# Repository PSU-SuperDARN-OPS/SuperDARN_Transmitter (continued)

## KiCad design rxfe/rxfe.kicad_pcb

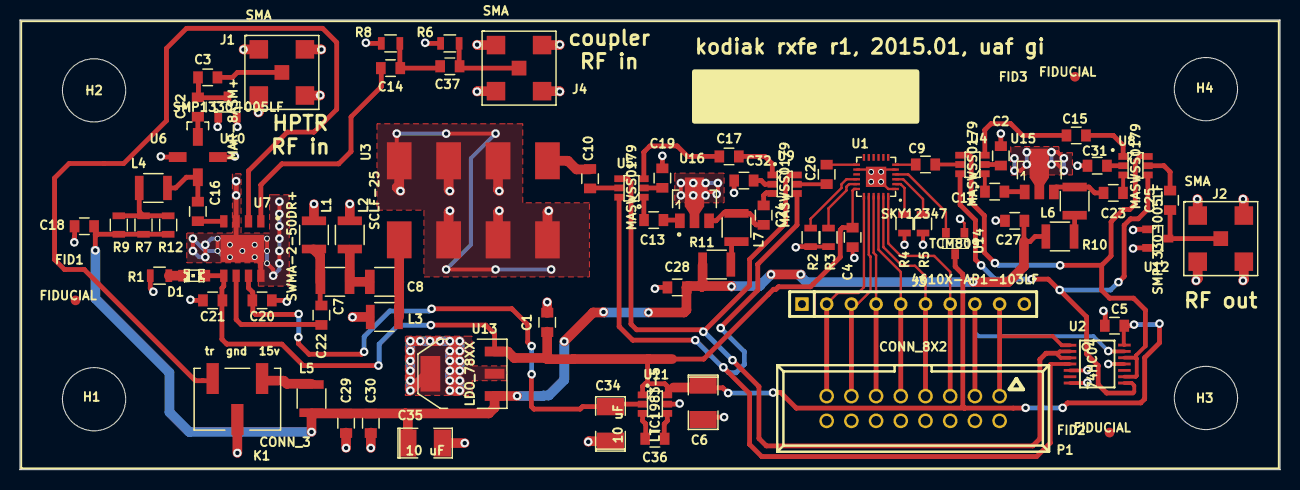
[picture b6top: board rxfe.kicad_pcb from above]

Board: 2 copper layers, 129.5 x 46.2 mm, 85 parts (0 on the bottom side), 65 nets.

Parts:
C1, C4, C5, C18, C20, C21, C27, C28, C29: 100 nF; C_0805
C2, C3, C9, C10, C11, C12, C13, C14, C15, C16, C17, C19, C22, C23, C24, C25, C26, C31, C32, C37: 22 nF; C_0805
C6, C34, C35: 10 uF; SMD-1210_Pol
C7, C8: 680pF; C_1210
C30, C36: 1 uF; C_0805
D1: LED; LED-0805
FID1, FID2, FID3: FIDUCIAL; FID_1MM
H1, H2, H3, H4: MOUNTING_HOLE; MountingHole_6-5mm
J1, J2, J4: SMA; SMA_0732511350
J3: 4610X-AP1-103LF; SIL-10
K1: CONN_3; 0740991003
L1, L3, L4, L5, L6, L7: 3.9uH; R_1210
L2: 1.2uH; R_1210
P1: CONN_8X2; VASCH8x2
R1, R2, R3, R4, R5, R7, R9, R12: 1k; R_0805
R6, R8: DNP; R_0805
R10, R11: 93.1; R_1210
U1: SKY12347; qfn24
U2: 74HC04; TSSOP14
U3: SCLF-25; YY161
U4, U5, U8, U9: MASWSS0179; SOT-23-6
U6: MAR-8ASM+; WW107
U7: SWMA-2-50DR+; DL1020
U10, U12: SMP1330-005LF; SOT-23
U11: LTC1983-5; SOT-23-6
U13: LDO_78XX; SOT-223
U14: TCM809; SOT-23
U15, U16: GALI-84+; SOT89-3_Housing

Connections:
-5V: C20.1, C34.2, U7.7, U11.2
/AMP1: U2.4, U5.6, U9.4
/AMP1CTL: J3.9, P1.1, U2.1
/AMP2: U2.8, U4.6, U8.4
/AMP2CTL: J3.8, P1.3, U2.13
/T/R: K1.3, U7.2
/~AMP1: U2.2, U2.3, U5.4, U9.6
/~AMP2: U2.9, U2.12, U4.4, U8.6
GND: C1.2, C2.1, C4.2, C5.2, C6.2, C18.1, C19.1, C20.2, C21.1, C27.1, C28.1, C29.2, C30.2, C31.2, C32.2, C34.1, C35.2, J1.2, J1.3, J1.4, J1.5, J2.2, J2.3, J2.4, J2.5, J3.1, J3.10, J4.2, J4.3, J4.4, J4.5, K1.2, L1.2, L2.2, L3.2, P1.2, P1.4, P1.6, P1.8, P1.10, P1.12, P1.14, P1.16, R1.2, R2.2, R3.2, R4.2, R5.2, R6.1, R8.1, U1.1, U1.5, U1.14, U1.25, U2.5, U2.7, U2.11, U3.2, U3.3, U3.4, U3.5, U3.6, U3.7, U6.2, U6.4, U7.3, U7.8, U7.EP, U10.1, U10.2, U11.5, U12.1, U12.2, U13.2, U13.4, U14.1, U15.2, U16.2
unnamed: C2.2, U4.2
unnamed: C3.2, J1.1
unnamed: C7.1, C8.2, L2.1
unnamed: C8.1, L3.1, U3.1
unnamed: C9.1, U4.5
unnamed: C9.2, U1.6
unnamed: C10.1, U5.5
unnamed: C10.2, U3.8
unnamed: C11.1, U15.1
unnamed: C11.2, U4.1
unnamed: C12.1, U6.1
unnamed: C3.1, C12.2, U10.3
unnamed: C13.1, U16.1
unnamed: C13.2, U5.1
unnamed: C14.1, U7.1
unnamed: C14.2, C37.1, R8.2
unnamed: C15.1, U8.1
unnamed: C15.2, U4.3
unnamed: C16.1, U7.4
unnamed: C16.2, L4.1, U6.3
unnamed: C17.1, U9.1
unnamed: C17.2, U5.3
unnamed: C19.2, U5.2
unnamed: C22.1, U7.6
unnamed: C7.2, C22.2, L1.1
unnamed: C23.1, U8.3
unnamed: C23.2, L6.1, U15.3
unnamed: C24.1, U9.3
unnamed: C24.2, L7.1, U16.3
unnamed: C25.1, J2.1, U12.3
unnamed: C25.2, U8.5
unnamed: C26.1, U1.13
unnamed: C26.2, U9.5
unnamed: C31.1, U8.2
unnamed: C32.1, U9.2
unnamed: C36.1, U11.4
unnamed: C36.2, U11.3
unnamed: C37.2, J4.1, R6.2
unnamed: D1.2, R1.1
unnamed: J3.2, P1.15, U1.19
unnamed: J3.3, P1.13, U1.20
unnamed: J3.4, P1.11, U1.21
unnamed: J3.5, P1.9, U1.22
unnamed: J3.6, P1.7, U1.23
unnamed: J3.7, P1.5, U1.24
unnamed: K1.1, L5.2
unnamed: L4.2, R7.2, R9.2, R12.2
unnamed: L6.2, R10.2
unnamed: L7.2, R11.2
unnamed: R2.1, U1.16
unnamed: R3.1, U1.17
unnamed: R4.1, U1.2
unnamed: R5.1, U1.3
unnamed: U1.4, U14.2
VCC: C1.1, C4.1, C5.1, C6.1, C21.2, D1.1, U1.18, U2.14, U7.5, U11.1, U11.6, U13.3, U14.3
VDD: C18.2, C27.2, C28.2, C29.1, C30.1, C35.1, L5.1, R7.1, R9.1, R10.1, R11.1, R12.1, U13.1

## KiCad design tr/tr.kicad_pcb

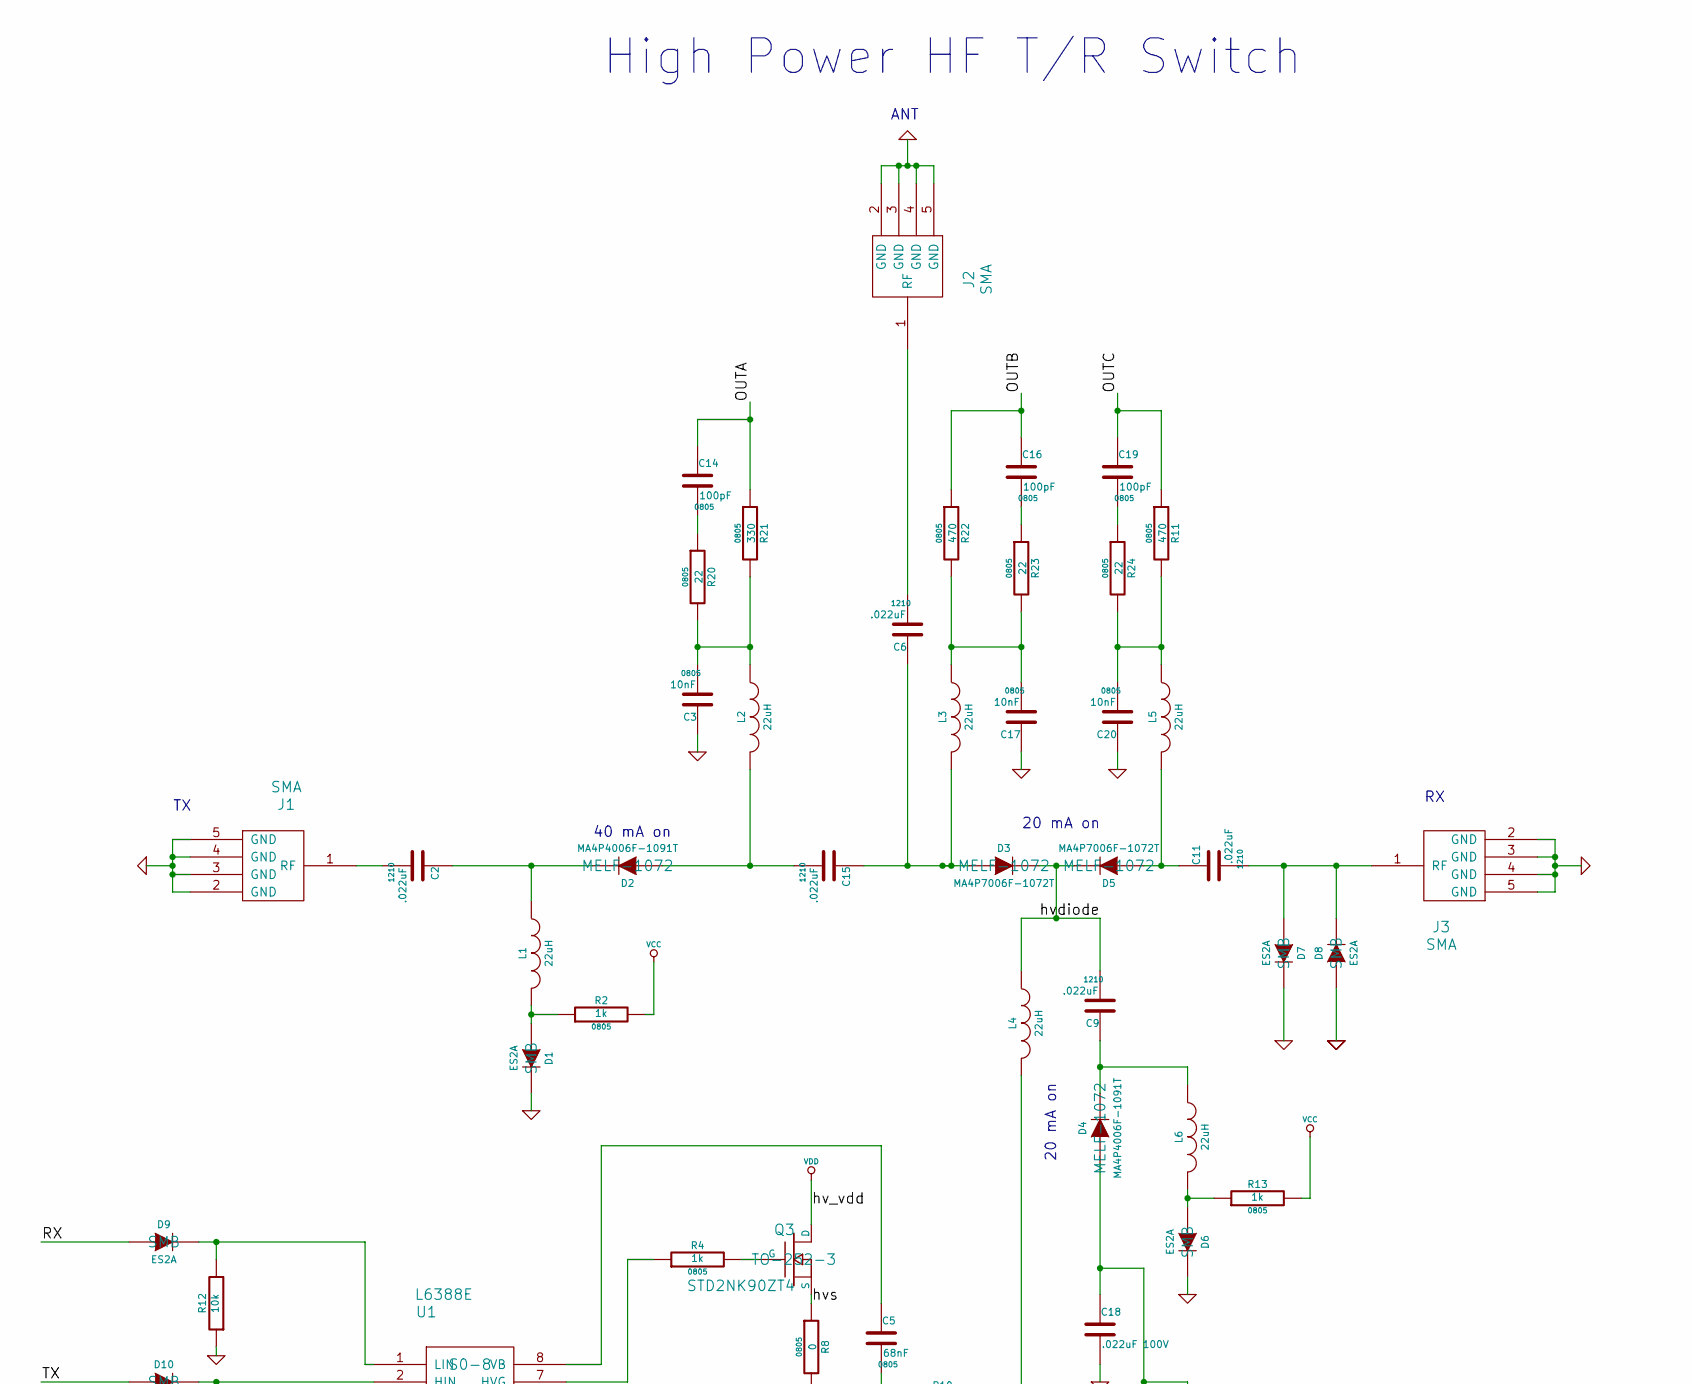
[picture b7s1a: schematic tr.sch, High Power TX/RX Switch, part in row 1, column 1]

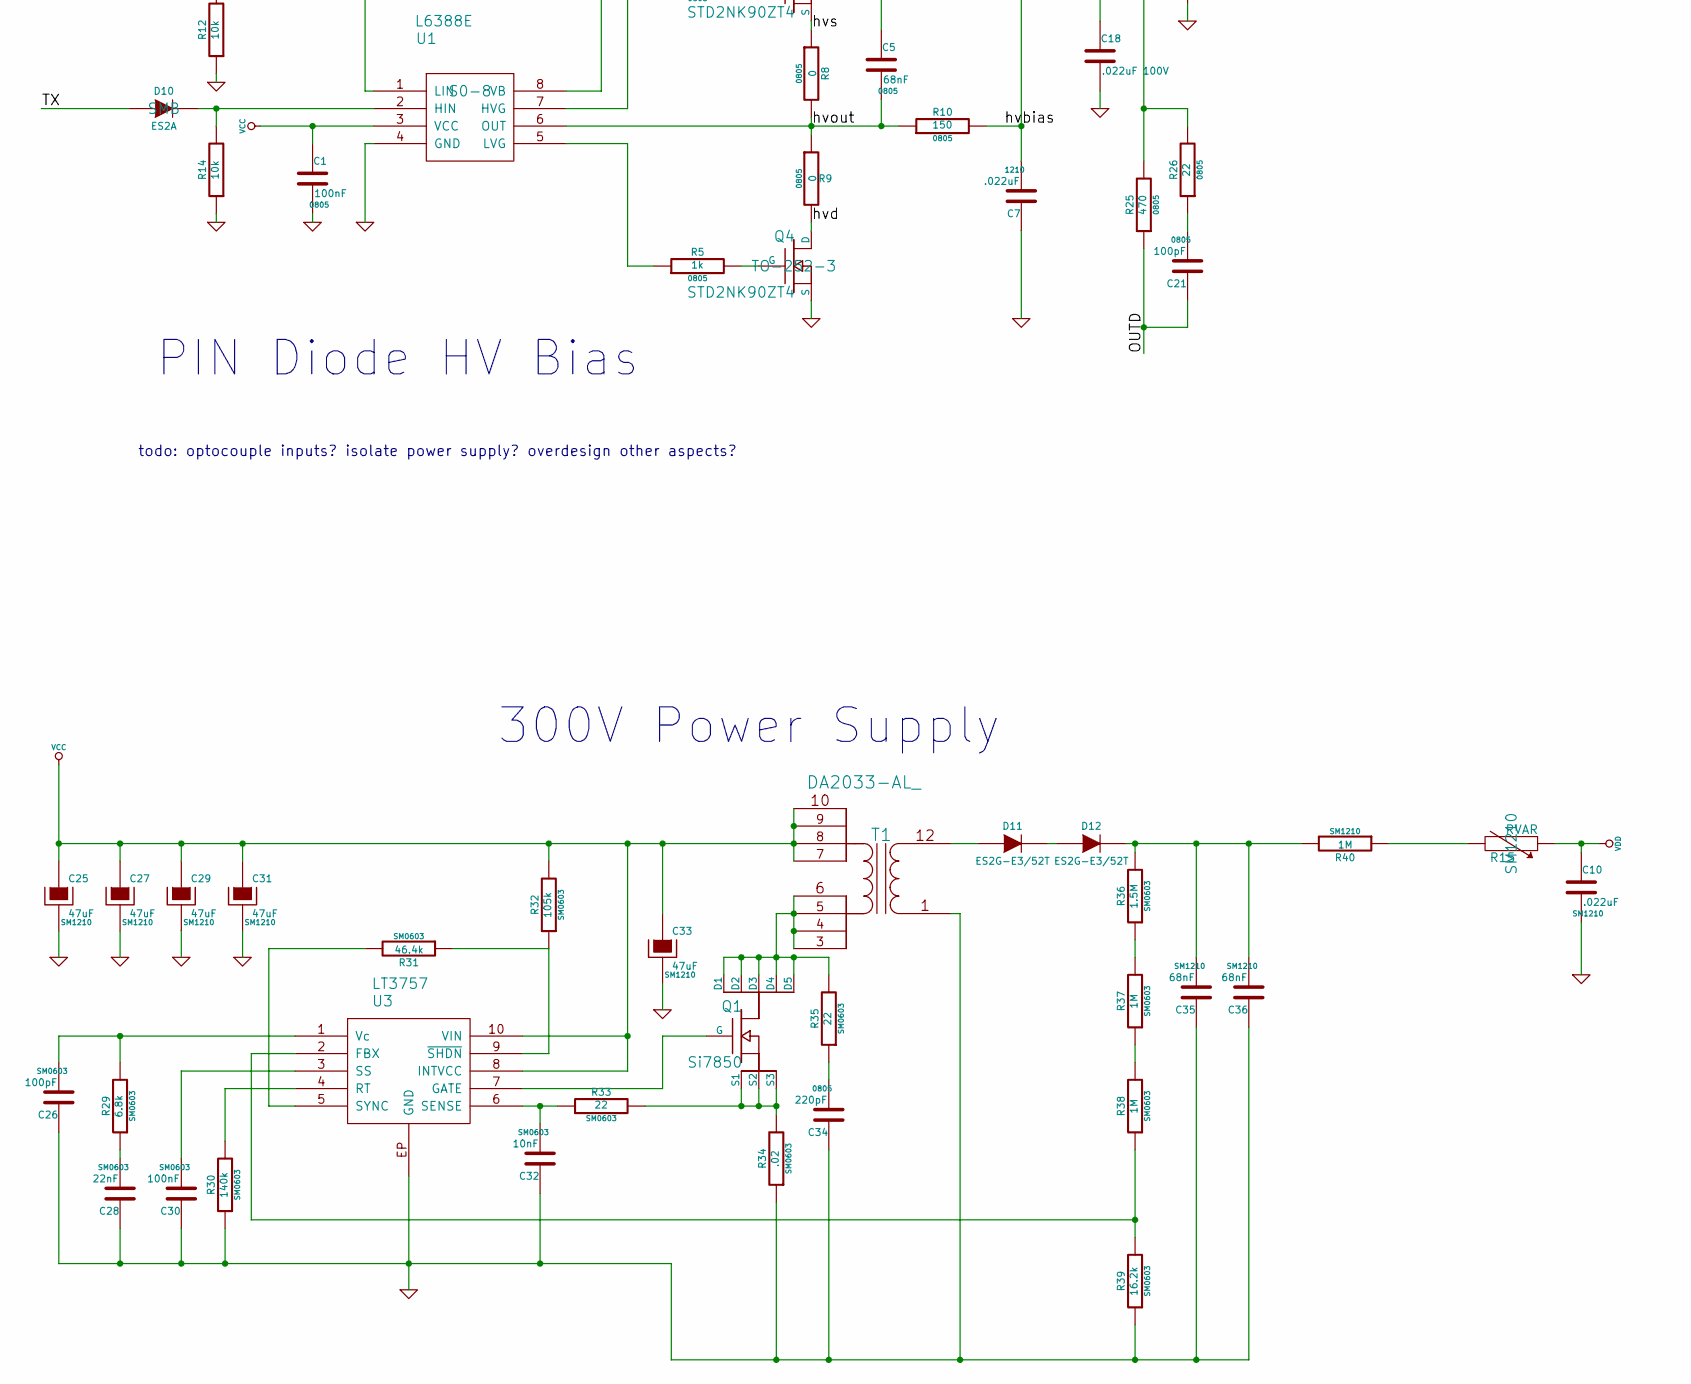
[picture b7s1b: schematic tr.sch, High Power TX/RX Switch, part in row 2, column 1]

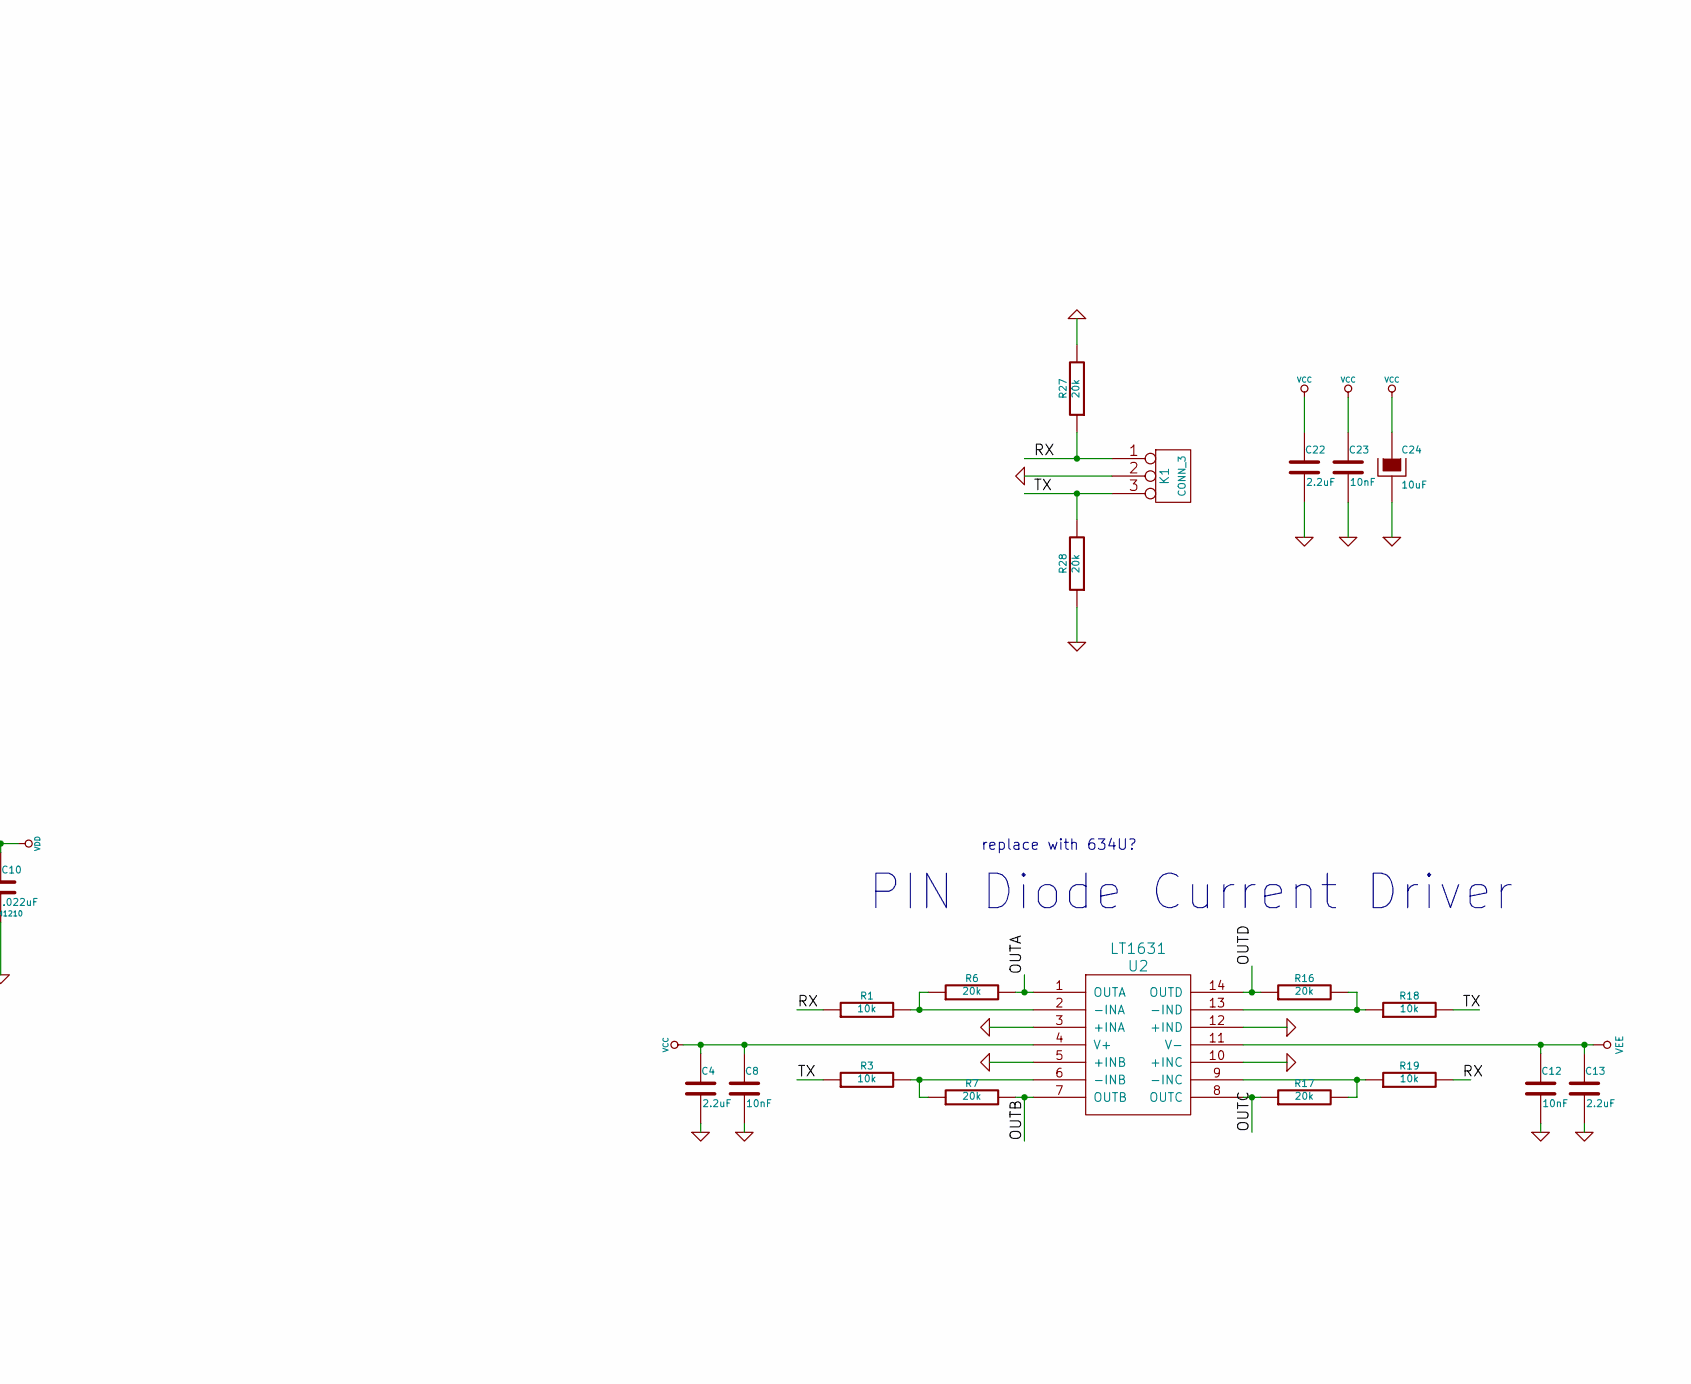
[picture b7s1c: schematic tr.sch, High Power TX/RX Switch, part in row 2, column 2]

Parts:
C1: 100nF; 0805
C2, C6, C7, C9, C11, C15: .022uF; 1210
C3, C17, C20: 10nF; 0805
C4, C13, C22: 2.2uF
C5: 68nF; 0805
C8, C12, C23: 10nF
C10: .022uF; SM1210
C14, C16, C19, C21: 100pF; 0805
C18: .022uF 100V
C24: 10uF
C25, C27, C29, C31, C33: 47uF; SM1210; DIGIKEYPN GRM32ER61C476ME15L
C26: 100pF; SM0603
C28: 22nF; SM0603
C30: 100nF; SM0603
C32: 10nF; SM0603
C34: 220pF; 0805
C35, C36: 68nF; SM1210; DIGIKEYPN C3225X7R2J683K
D1, D6, D7, D8, D9, D10: ES2A; SMB
D2, D4: MA4P4006F-1091T; MELF-1072
D3, D5: MA4P7006F-1072T; MELF-1072
D11, D12: ES2G-E3/52T
J1, J2, J3: SMA
K1: CONN_3
L1, L2, L3, L4, L5, L6: 22uH
Q1: Si7850
Q3, Q4: STD2NK90ZT4; TO-252-3
R1, R3, R12, R14, R18, R19: 10k
R2, R4, R5, R13: 1k; 0805
R6, R7, R16, R17, R27, R28: 20k
R8, R9: 0; 0805
R10: 150; 0805
R11, R22, R25: 470; 0805
R15: RVAR; SM1210
R20, R23, R24, R26: 22; 0805
R21: 330; 0805
R29: 6.8k; SM0603
R30: 140k; SM0603
R31: 46.4k; SM0603
R32: 105k; SM0603
R33, R35: 22; SM0603
R34: .02; SM0603
R36: 1.5M; SM0603
R37, R38: 1M; SM0603
R39: 16.2k; SM0603
R40: 1M; SM1210
T1: DA2033-AL_
U1: L6388E; S0-8
U2: LT1631
U3: LT3757

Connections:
/OUTA: C14.1, R6.2, R21.1, U2.1 (OUTA)
/OUTB: C16.1, R7.2, R22.1, U2.7 (OUTB)
/OUTC: C19.1, R11.1, R17.1, U2.8 (OUTC)
/OUTD: C21.1, R16.1, R25.1, U2.14 (OUTD)
/RX: D9.1 (A), K1.1, R1.1, R19.2, R27.1
/TX: D10.1 (A), K1.3, R3.1, R18.2, R28.2
/hvbias: C7.2, L4.2, R10.2
/hvd: Q4.D, R9.2
/hvdiode: C9.2, D3.2 (K), D5.2 (K), L4.1
/hvout: C5.2, R8.2, R9.1, R10.1, U1.6 (OUT)
/hvs: Q3.S, R8.1
GND: C1.2, C3.1, C4.2, C7.1, C8.2, C10.2, C12.2, C13.2, C17.1, C18.2, C20.1, C22.2, C23.2, C24.2, C25.2, C26.1, C27.2, C28.1, C29.2, C30.1, C31.2, C32.1, C33.2, C34.1, C35.1, C36.1, D1.2 (K), D6.2 (K), D7.2 (K), D8.1 (A), J1.2 (GND), J1.3 (GND), J1.4 (GND), J1.5 (GND), J2.2 (GND), J2.3 (GND), J2.4 (GND), J2.5 (GND), J3.2 (GND), J3.3 (GND), J3.4 (GND), J3.5 (GND), K1.2 (PM), Q4.S, R12.1, R14.1, R27.2, R28.1, R30.1, R34.1, R39.1, T1.1 (SDOT), U1.4 (GND), U2.3 (+INA), U2.5 (+INB), U2.10 (+INC), U2.12 (+IND), U3.EP (GND)
unnamed: R3.2, R7.1, U2.6 (-INB)
unnamed: R1.2, R6.1, U2.2 (-INA)
unnamed: R16.2, R18.1, U2.13 (-IND)
unnamed: R17.2, R19.1, U2.9 (-INC)
unnamed: C18.1, D4.1 (A), R25.2, R26.2
unnamed: C21.2, R26.1
unnamed: C16.2, R23.1
unnamed: C17.2, L3.1, R22.2, R23.2
unnamed: C19.2, R24.1
unnamed: C14.2, R20.1
unnamed: C3.2, L2.1, R20.2, R21.2
unnamed: C6.2, J2.1 (RF)
unnamed: C11.2, D7.1 (A), D8.2 (K), J3.1 (RF)
unnamed: C2.1, D2.2 (K), L1.1
unnamed: C2.2, J1.1 (RF)
unnamed: D1.1 (A), L1.2, R2.1
unnamed: D6.1 (A), L6.2, R13.1
unnamed: C9.1, D4.2 (K), L6.1
unnamed: R5.1, U1.5 (LVG)
unnamed: Q3.G, R4.2
unnamed: Q4.G, R5.2
unnamed: C5.1, U1.8 (VB)
unnamed: C15.2, D2.1 (A), L2.2
unnamed: R15.2, R40.1
unnamed: Q1.1 (S1), Q1.2 (S2), Q1.3 (S3), R33.2, R34.2
unnamed: C34.2, R35.1
unnamed: C35.2, C36.2, D12.2 (K), R36.2, R40.2
unnamed: D11.1 (A), T1.12 (S)
unnamed: D11.2 (K), D12.1 (A)
unnamed: Q1.4 (G), U3.7 (GATE)
unnamed: Q1.5 (D1), Q1.6 (D2), Q1.7 (D3), Q1.8 (D4), Q1.9 (D5), R35.2, T1.3, T1.4, T1.5, T1.6
unnamed: D10.2 (K), R14.2, U1.2 (HIN)
unnamed: D9.2 (K), R12.2, U1.1 (LIN)
unnamed: R30.2, U3.4 (RT)
unnamed: R31.2, U3.5 (SYNC)
unnamed: R31.1, R32.1, U3.9 (~SHDN)
unnamed: R38.1, R39.2, U3.2 (FBX)
unnamed: R37.1, R38.2
unnamed: R36.1, R37.2
unnamed: C26.2, R29.2, U3.1 (Vc)
unnamed: C32.2, R33.1, U3.6 (SENSE)
unnamed: C28.2, R29.1
unnamed: C30.2, U3.3 (SS)
unnamed: R4.1, U1.7 (HVG)
unnamed: C11.1, D5.1 (A), L5.2
unnamed: C20.2, L5.1, R11.2, R24.2
unnamed: C6.1, C15.1, D3.1 (A), L3.2
VCC: C1.1, C4.1, C8.1, C22.1, C23.1, C24.1, C25.1, C27.1, C29.1, C31.1, C33.1, R2.2, R13.2, R32.2, T1.7 (PDOT), T1.8 (PDOT), T1.9 (PDOT), T1.10 (PDOT), U1.3 (VCC), U2.4 (V+), U3.8 (INTVCC), U3.10 (VIN)
VDD: C10.1, Q3.D, R15.1
VEE: C12.1, C13.1, U2.11 (V-)

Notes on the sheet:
ANT
40 mA on
20 mA on
20 mA on
300V Power Supply
PIN Diode Current Driver
PIN Diode HV Bias
High Power HF T/R Switch
replace with 634U?
todo: optocouple inputs? isolate power supply? overdesign other aspects?

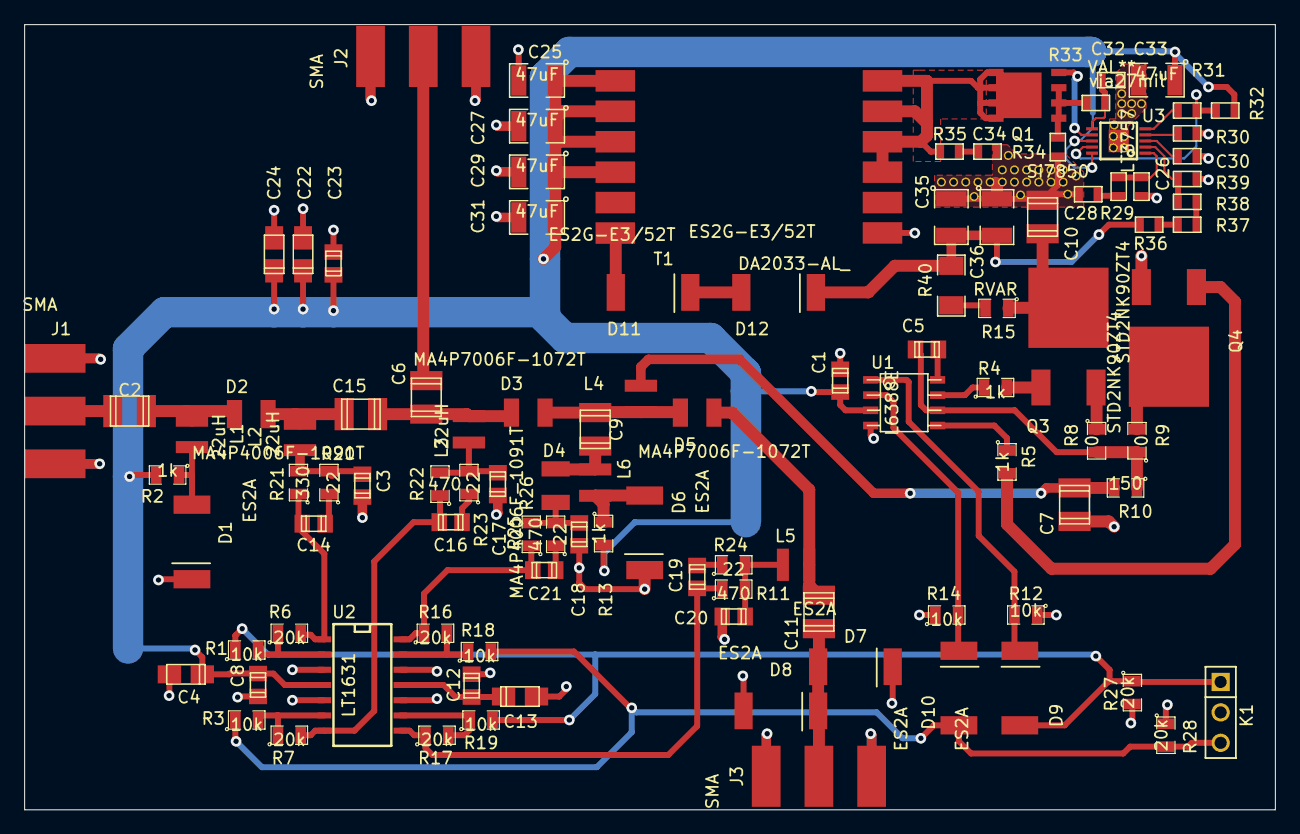
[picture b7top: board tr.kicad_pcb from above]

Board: 4 copper layers, 104.4 x 65.5 mm, 106 parts (0 on the bottom side), 62 nets.

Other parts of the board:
via27mil: VAL**; via27mil
